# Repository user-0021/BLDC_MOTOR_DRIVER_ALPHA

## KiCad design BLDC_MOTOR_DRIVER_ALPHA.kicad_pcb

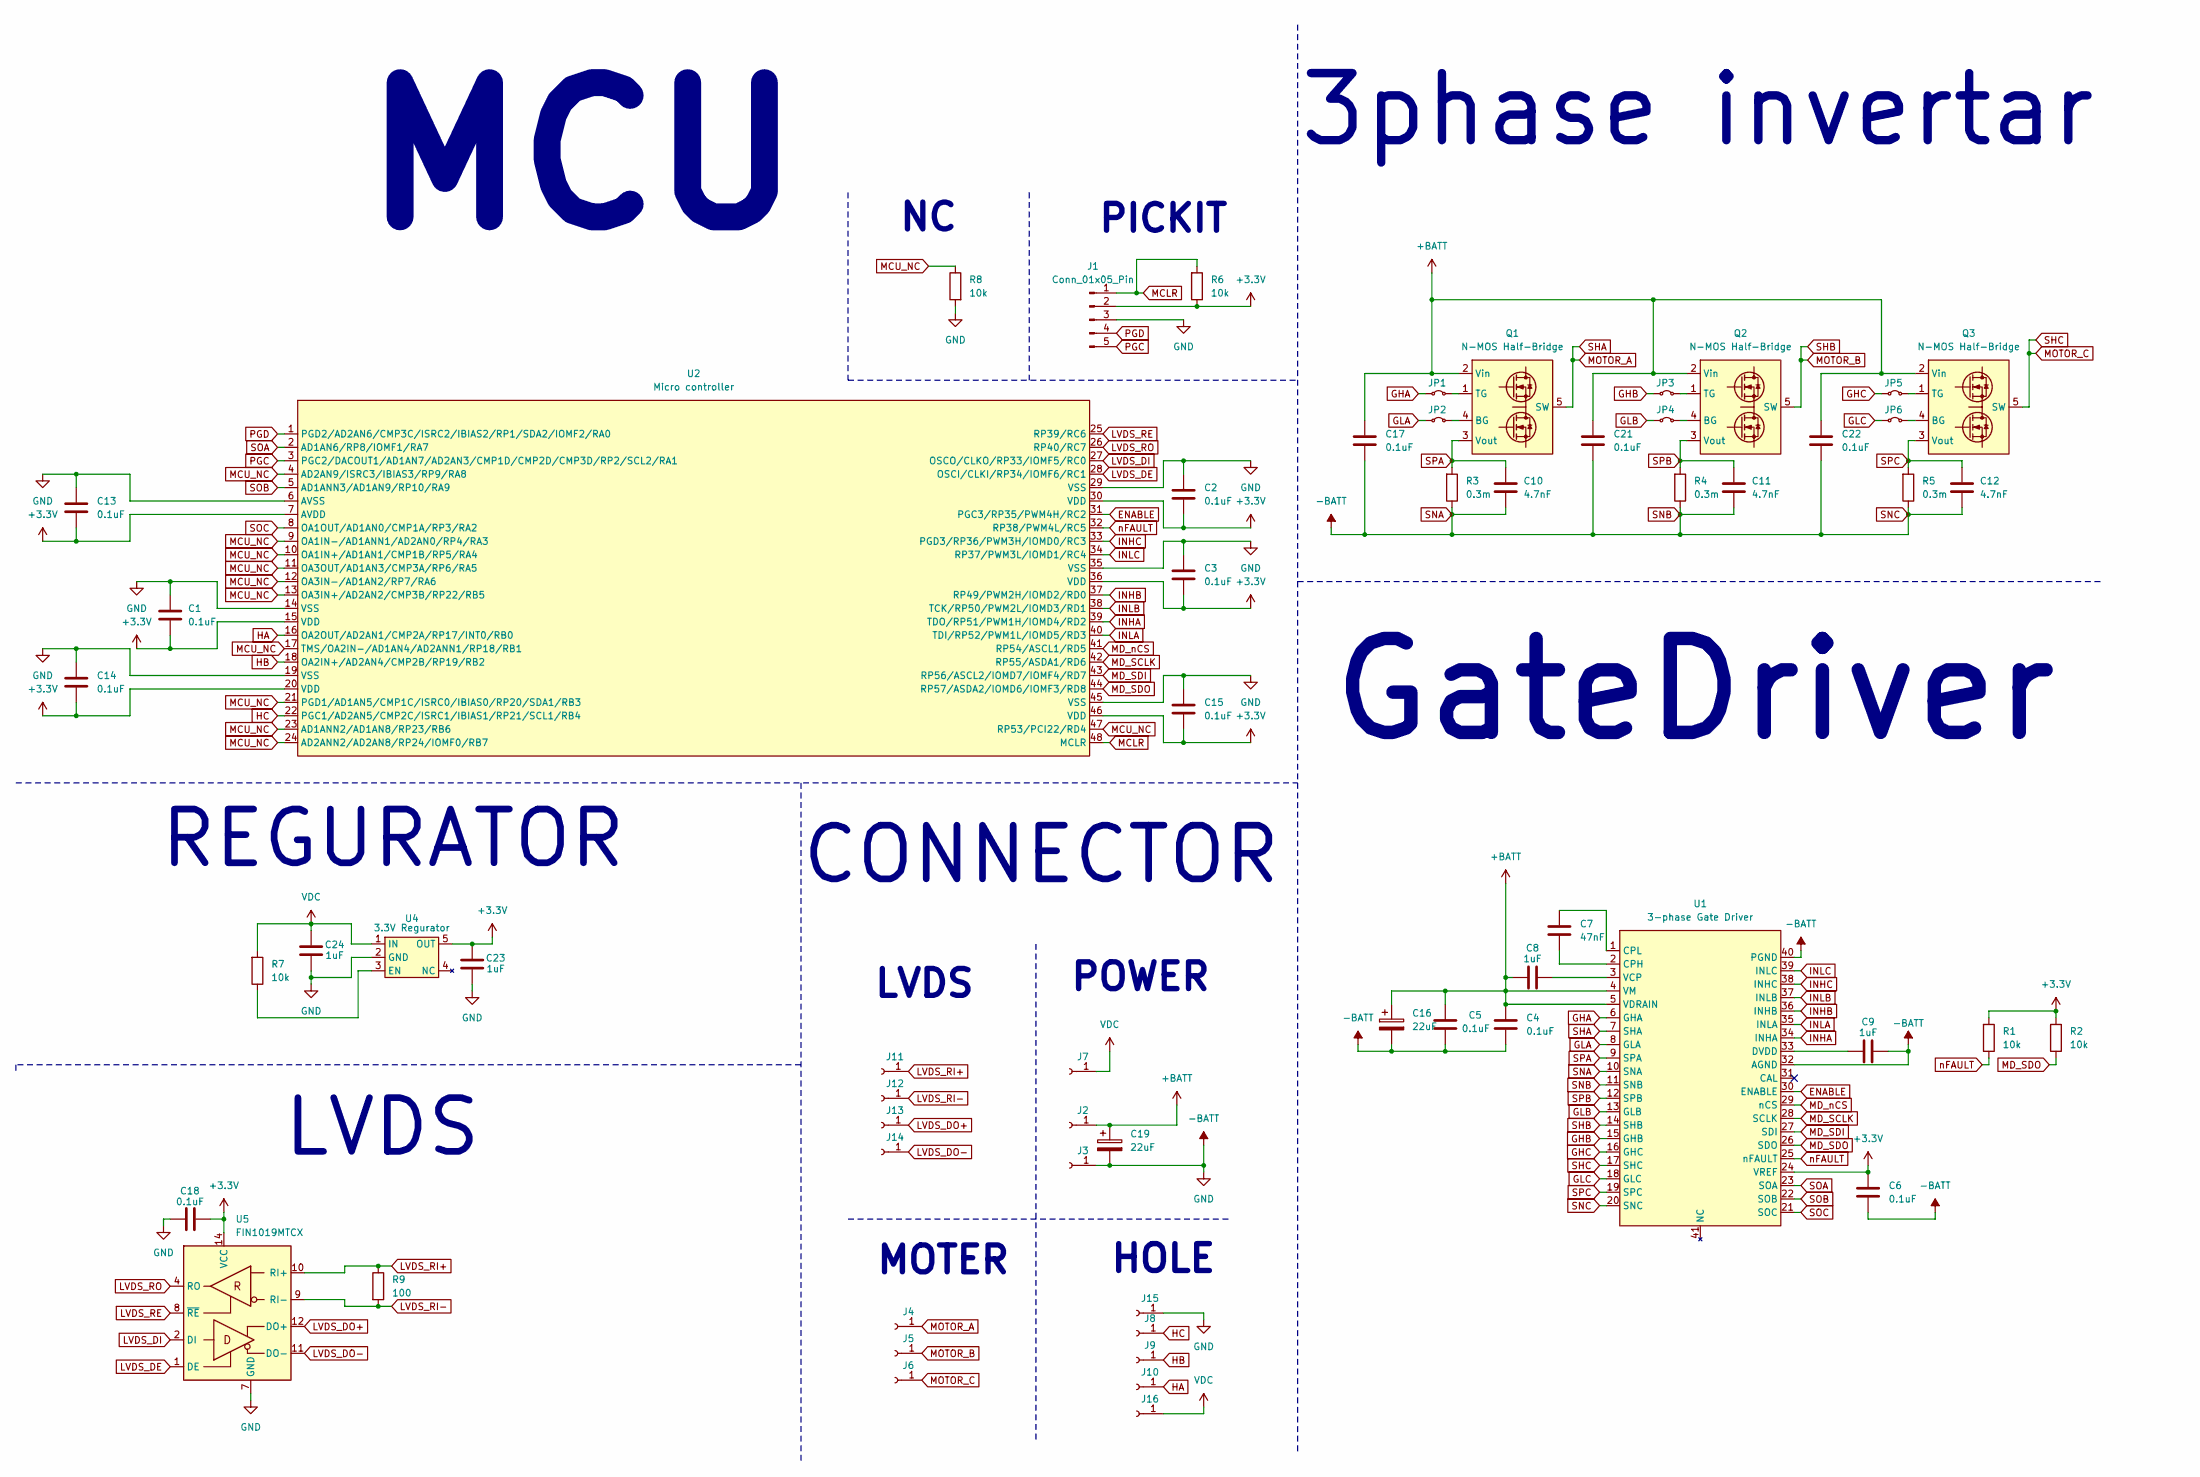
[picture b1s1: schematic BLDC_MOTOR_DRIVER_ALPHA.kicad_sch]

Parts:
C1, C2, C3, C4, C5, C6, C13, C14, C15, C17, C18, C21, C22: 0.1uF; C_0603_1608Metric; digikey none
C7: 47nF; C_0402_1005Metric; digikey 445-6897-1-ND
C8, C9, C23, C24: 1uF; C_0805_2012Metric; digikey 1276-1029-1-ND
C10, C11, C12: 4.7nF; C_0603_1608Metric; digikey 311-1083-1-ND
C16, C19: 22uF; CP_Elec_5x5.3; digikey 732-8505-1-ND
J1: Conn_01x05_Pin; PinHeader_1x05_P2.54mm_Vertical
J2, J3, J4, J5, J6: Conn_01x01_Socket; SolderWirePad_1x01_SMD_3x6mm
J7, J8, J9, J10, J11, J12, J13, J14, J15, J16: Conn_01x01_Socket; SolderWirePad_1x01_SMD_2x4mm
JP1, JP2, JP3, JP4, JP5, JP6: Jumper_2_Small_Bridged; R_0402_1005Metric
Q1, Q2, Q3: N-MOS Half-Bridge; CSD87588N; digikey 296-35792-1-ND
R1, R2, R6, R7, R8: 10k; R_0603_1608Metric; digikey 4988-NRC06F1002TRFCT-ND
R3, R4, R5: 0.3m; R_2512_6332Metric; digikey 738-CSNL2512FTL300CT-ND
R9: 100; R_0402_1005Metric; digikey 2019-RK73H1ETTP1000FCT-ND
U1: 3-phase Gate Driver; TB67Z833SFTG; digikey 264-TB67Z833SFTG(O,EL)CT-ND
U2: Micro controller; TQFP-48_7x7mm_P0.5mm; digikey 150-DSPIC33AK32MC105-I/PT-ND
U4: 3.3V Regurator; SOT-23-5; digikey 296-TLV74033PDBVRCT-ND
U5: FIN1019MTCX; TSSOP-14_4.4x5mm_P0.65mm; digikey FIN1019MTCXCT-ND

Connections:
+3.3V: C1.2, C2.2, C3.2, C6.1, C13.2, C14.2, C15.2, C18.1, C23.1, J1.2, R1.1, R2.1, R6.2, U1.24 (VREF), U2.7 (AVDD), U2.15 (VDD), U2.20 (VDD), U2.30 (VDD), U2.36 (VDD), U2.46 (VDD), U4.5 (OUT), U5.14 (VCC)
+BATT: C4.1, C5.2, C8.1, C16.1, C17.1, C19.1, C21.1, C22.1, J2.1, Q1.2 (Vin), Q2.2 (Vin), Q3.2 (Vin), U1.4 (VM), U1.5 (VDRAIN)
ENABLE: U1.30 (ENABLE), U2.31 (PGC3/RP35/PWM4H/RC2)
GHA: JP1.1 (A), U1.6 (GHA)
GHB: JP3.1 (A), U1.15 (GHB)
GHC: JP5.1 (A), U1.16 (GHC)
GLA: JP2.1 (A), U1.8 (GLA)
GLB: JP4.1 (A), U1.13 (GLB)
GLC: JP6.1 (A), U1.18 (GLC)
HA: J10.1, U2.16 (OA2OUT/AD2AN1/CMP2A/RP17/INT0/RB0)
HB: J9.1, U2.18 (OA2IN+/AD2AN4/CMP2B/RP19/RB2)
HC: J8.1, U2.22 (PGC1/AD2AN5/CMP2C/ISRC1/IBIAS1/RP21/SCL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)
INHA: U1.34 (INHA), U2.39 (TDO/RP51/PWM1H/IOMD4/RD2)
INHB: U1.36 (INHB), U2.37 (RP49/PWM2H/IOMD2/RD0)
INHC: U1.38 (INHC), U2.33 (PGD3/RP36/PWM3H/IOMD0/RC3)
INLA: U1.35 (INLA), U2.40 (TDI/RP52/PWM1L/IOMD5/RD3)
INLB: U1.37 (INLB), U2.38 (TCK/RP50/PWM2L/IOMD3/RD1)
INLC: U1.39 (INLC), U2.34 (RP37/PWM3L/IOMD1/RC4)
LVDS_DE: U2.28 (OSCI/CLKI/RP34/IOMF6/RC1), U5.1 (DE)
LVDS_DI: U2.27 (OSCO/CLKO/RP33/IOMF5/RC0), U5.2 (DI)
LVDS_DO+: J13.1, U5.12 (DO+)
LVDS_DO-: J14.1, U5.11 (DO-)
LVDS_RE: U2.25 (RP39/RC6), U5.8 (~RE)
LVDS_RI+: J11.1, R9.1, U5.10 (RI+)
LVDS_RI-: J12.1, R9.2, U5.9 (RI-)
LVDS_RO: U2.26 (RP40/RC7), U5.4 (RO)
MCLR: J1.1, R6.1, U2.48 (MCLR)
MCU_NC: R8.2, U2.4 (AD2AN9/ISRC3/IBIAS3/RP9/RA8), U2.9 (OA1IN-/AD1ANN1/AD2AN0/RP4/RA3), U2.10 (OA1IN+/AD1AN1/CMP1B/RP5/RA4), U2.11 (OA3OUT/AD1AN3/CMP3A/RP6/RA5), U2.12 (OA3IN-/AD1AN2/RP7/RA6), U2.13 (OA3IN+/AD2AN2/CMP3B/RP22/RB5), U2.17 (TMS/OA2IN-/AD1AN4/AD2ANN1/RP18/RB1), U2.21 (PGD1/AD1AN5/CMP1C/ISRC0/IBIAS0/RP20/SDA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), U2.23 (AD1ANN2/AD1AN8/RP23/RB6), U2.24 (AD2ANN2/AD2AN8/RP24/IOMF0/RB7), U2.47 (RP53/PCI22/RD4)
MD_SCLK: U1.28 (SCLK), U2.42 (RP55/ASDA1/RD6)
MD_SDI: U1.27 (SDI), U2.43 (RP56/ASCL2/IOMD7/IOMF4/RD7)
MD_SDO: R2.2, U1.26 (SDO), U2.44 (RP57/ASDA2/IOMD6/IOMF3/RD8)
MD_nCS: U1.29 (nCS), U2.41 (RP54/ASCL1/RD5)
MOTOR_A: J4.1, Q1.5 (SW), U1.7 (SHA)
MOTOR_B: J5.1, Q2.5 (SW), U1.14 (SHB)
MOTOR_C: J6.1, Q3.5 (SW), U1.17 (SHC)
unnamed: JP1.2 (B), Q1.1 (TG)
unnamed: JP2.2 (B), Q1.4 (BG)
unnamed: JP3.2 (B), Q2.1 (TG)
unnamed: JP4.2 (B), Q2.4 (BG)
unnamed: JP5.2 (B), Q3.1 (TG)
unnamed: JP6.2 (B), Q3.4 (BG)
unnamed: C7.2, U1.2 (CPH)
unnamed: C7.1, U1.1 (CPL)
unnamed: C9.1, U1.33 (DVDD)
unnamed: C8.2, U1.3 (VCP)
unnamed: R7.2, U4.3 (EN)
PGC: J1.5, U2.3 (PGC2/DACOUT1/AD1AN7/AD2AN3/CMP1D/CMP2D/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)
PGD: J1.4, U2.1 (PGD2/AD2AN6/CMP3C/ISRC2/IBIAS2/RP1/SDA2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)
SNA: C1.1, C2.1, C3.1, C4.2, C5.1, C6.2, C9.2, C10.2, C11.2, C12.2, C13.1, C14.1, C15.1, C16.2, C17.2, C18.2, C19.2, C21.2, C22.2, C23.2, C24.2, J1.3, J3.1, J15.1, R3.2, R4.2, R5.2, R8.1, U1.10 (SNA), U1.11 (SNB), U1.20 (SNC), U1.32 (AGND), U1.40 (PGND), U2.6 (AVSS), U2.14 (VSS), U2.19 (VSS), U2.29 (VSS), U2.35 (VSS), U2.45 (VSS), U4.2 (GND), U5.7 (GND)
SOA: U1.23 (SOA), U2.2 (AD1AN6/RP8/IOMF1/RA7)
SOB: U1.22 (SOB), U2.5 (AD1ANN3/AD1AN9/RP10/RA9)
SOC: U1.21 (SOC), U2.8 (OA1OUT/AD1AN0/CMP1A/RP3/RA2)
SPA: C10.1, Q1.3 (Vout), R3.1, U1.9 (SPA)
SPB: C11.1, Q2.3 (Vout), R4.1, U1.12 (SPB)
SPC: C12.1, Q3.3 (Vout), R5.1, U1.19 (SPC)
VDC: C24.1, J7.1, J16.1, R7.1, U4.1 (IN)
nFAULT: R1.2, U1.25 (nFAULT), U2.32 (RP38/PWM4L/RC5)

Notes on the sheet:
GateDriver
HOLE
PICKIT
CONNECTOR
3phase invertar
MOTER
LVDS
MCU
REGURATOR
POWER

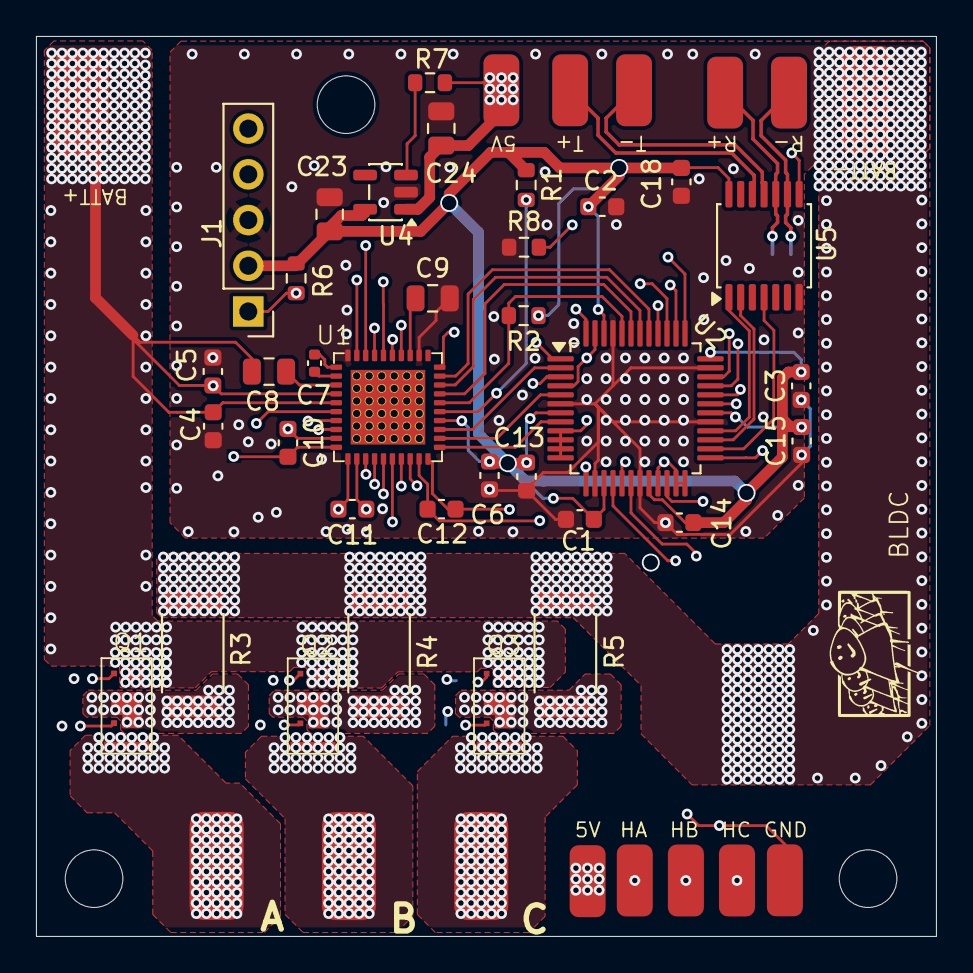
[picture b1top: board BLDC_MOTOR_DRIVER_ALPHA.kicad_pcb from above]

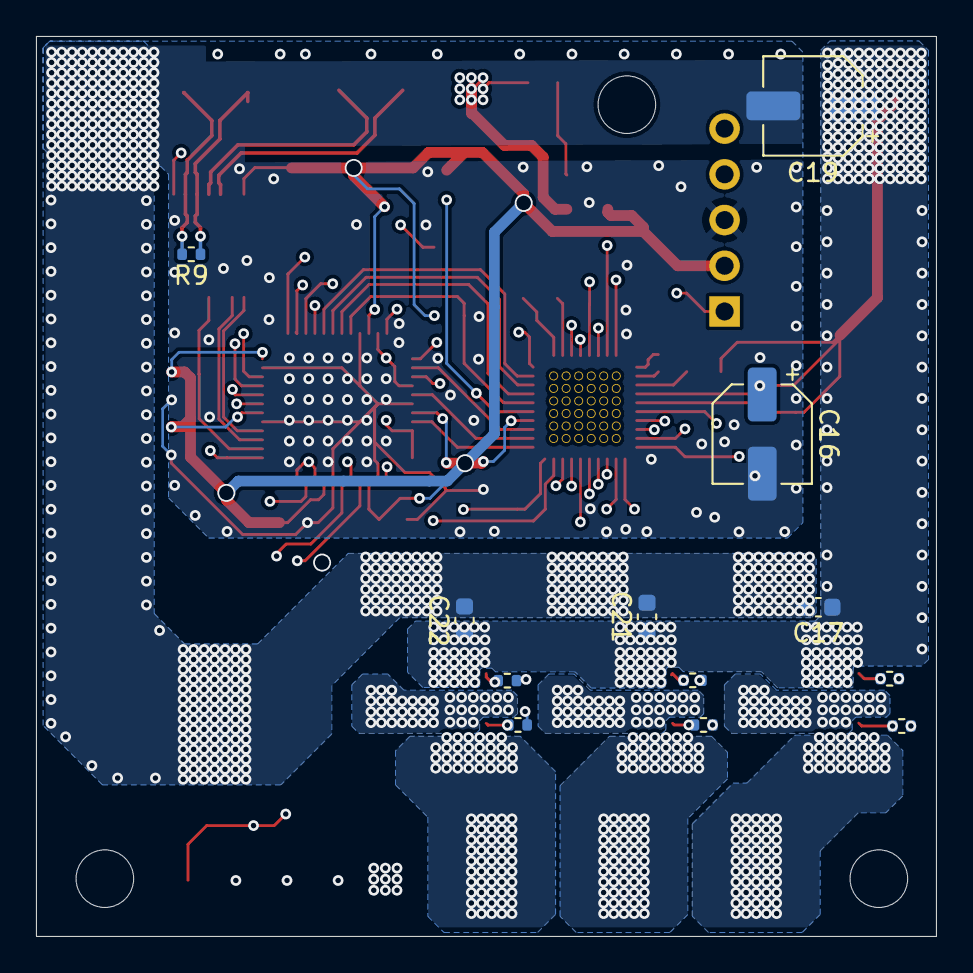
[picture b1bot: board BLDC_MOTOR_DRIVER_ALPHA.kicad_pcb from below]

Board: 8 copper layers, 50.0 x 50.0 mm, 61 parts (12 on the bottom side), 57 nets.

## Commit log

2025-10-29 first
2025-10-29 update lib
2025-11-09 dftg
2025-11-11 dsaf
2025-11-12 upda
2025-11-18 v1.0.0
2025-11-18 add readme
2025-11-18 add licence
2025-11-18 upfaet
